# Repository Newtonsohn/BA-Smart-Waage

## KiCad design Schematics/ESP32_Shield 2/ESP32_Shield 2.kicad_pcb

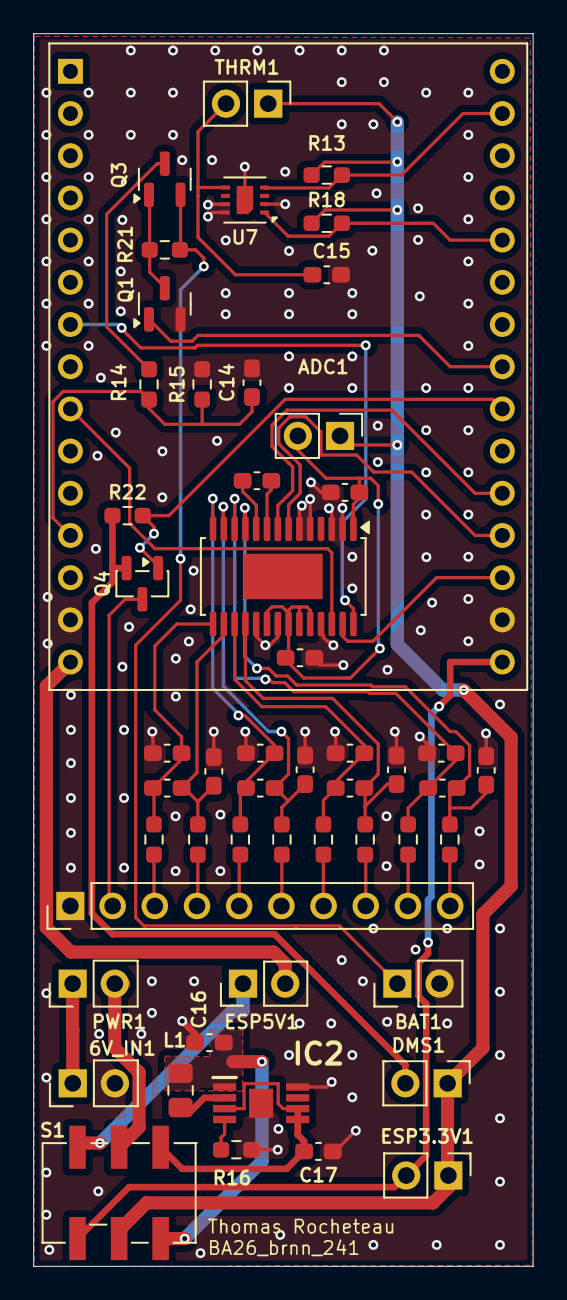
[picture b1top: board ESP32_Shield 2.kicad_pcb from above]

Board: 2 copper layers, 30.1 x 74.2 mm, 52 parts (0 on the bottom side), 46 nets.

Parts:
6V_IN1: Conn_01x02; PinHeader_1x02_P2.54mm_Vertical
ADC1: Conn_01x02; PinHeader_1x02_P2.54mm_Vertical
BAT1: Conn_01x02; PinHeader_1x02_P2.54mm_Vertical
C1, C12, C13, C14, C15: 0.1u; C_0603_1608Metric_Pad1.08x0.95mm_HandSolder
C16: 10u; C_0603_1608Metric_Pad1.08x0.95mm_HandSolder
C17: 4.7u; C_0603_1608Metric_Pad1.08x0.95mm_HandSolder
C18, C21, C24, C27: 1u; C_0603_1608Metric_Pad1.08x0.95mm_HandSolder
C19, C20, C22, C23, C25, C26, C28, C29: 10n; C_0603_1608Metric_Pad1.08x0.95mm_HandSolder
DMS1: Conn_01x02; PinHeader_1x02_P2.54mm_Vertical
ESP3.3V1, ESP5V1: Conn_01x02; PinHeader_1x02_P2.54mm_Vertical
IC2: TPS62842DGRR; SOP65P490X110-9N
J1: Conn_01x10; PinHeader_1x10_P2.54mm_Vertical
L1: 2.2u; C_0805_2012Metric_Pad1.18x1.45mm_HandSolder
PWR1: Conn_01x02; PinHeader_1x02_P2.54mm_Vertical
Q1: Si1308EDL; SOT-23
Q3, Q4: Si2319CDS; SOT-23
R13, R18: 10k; R_0603_1608Metric_Pad0.98x0.95mm_HandSolder
R14, R15, R21, R22: 100k; R_0603_1608Metric_Pad0.98x0.95mm_HandSolder
R16: 52.3k; R_0603_1608Metric_Pad0.98x0.95mm_HandSolder
R17, R19, R20, R23, R24, R25, R26, R27: 100; R_0603_1608Metric_Pad0.98x0.95mm_HandSolder
S1: JS202011SCQN; SW_DPDT_CK_JS202011JCQN
THRM1: Conn_01x02; PinHeader_1x02_P2.54mm_Vertical
U2: ESP32-C3-DevKitM-1
U6: ADS1234IPW; TSSOP-28-1EP_4.4x9.7mm_P0.65mm_EP2.74x4.75mm
U7: SHT30-DIS; Sensirion_DFN-8-1EP_2.5x2.5mm_P0.5mm_EP1.1x1.7mm

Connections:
3v3 BUCK: C16.2, IC2.1 (VOS), L1.1, S1.6
5V BUCK: C17.2, IC2.3 (MODE), IC2.5 (EN), IC2.6 (VIN), S1.3
5V LDO: ESP5V1.1, S1.1
!EN_DMS: Q4.1 (G), R22.1, U2.22 (IO17)
!PWDN: U2.9 (IO26), U6.26 (~PWDN)
+3.3V: ADC1.1, DMS1.1, ESP3.3V1.1, R13.2, R18.2, S1.5, THRM1.1
+5V: PWR1.2, S1.2
+BATT: BAT1.1, Q3.2 (S), R21.2
A0: U2.20 (IO4), U6.8 (A0)
A1: U2.19 (IO2), U6.7 (A1)
D_RDY_OUT: U2.7 (IO32), U6.28 (~DRDY/DOUT)
GND: 6V_IN1.2, BAT1.2, C1.1, C13.1, C14.1, C15.2, C16.1, C17.1, C19.1, C20.1, C22.1, C23.1, C25.1, C26.1, C28.1, C29.1, IC2.8 (GND_1), IC2.9 (GND_2), J1.1, Q1.2 (S), R15.1, R16.2, U2.14 (GND), U2.17 (GND), U6.2 (DGND), U6.3 (CLKIN/XTAL1), U6.5 (DGND), U6.6 (DGND), U6.19 (REFN), U6.21 (AGND), U6.25 (SPEED), U7.2 (ADDR), U7.7 (R), U7.8 (VSS), U7.9 (VSS)
N2: C24.1, C26.2, R25.2, U6.17 (AINN2)
N3: C21.1, C23.2, R23.2, U6.14 (AINN3)
N4: C18.1, C20.2, R17.2, U6.15 (AINN4)
unnamed: 6V_IN1.1, PWR1.1
unnamed: ADC1.2, C1.2, C13.2, U6.1 (DVDD), U6.20 (REFP), U6.22 (AVDD), U6.23 (GAIN0), U6.24 (GAIN1)
unnamed: C12.1, U6.10 (CAP)
unnamed: C12.2, U6.9 (CAP)
unnamed: DMS1.2, Q4.2 (S), R22.2
unnamed: ESP3.3V1.2, S1.4, U2.16 (3V3)
unnamed: ESP5V1.2, U2.15 (5V)
unnamed: IC2.2 (SW), L1.2
unnamed: IC2.4 (VSET), R16.1
unnamed: J1.2, Q4.3 (D)
unnamed: J1.3, R17.1
unnamed: J1.4, R19.1
unnamed: J1.5, R23.1
unnamed: J1.6, R20.1
unnamed: J1.7, R25.1
unnamed: J1.8, R24.1
unnamed: J1.9, R27.1
unnamed: J1.10, R26.1
unnamed: Q1.3 (D), Q3.1 (G), R21.1
unnamed: Q3.3 (D), R14.1
unnamed: C15.1, THRM1.2, U7.5 (VDD)
unnamed: C27.1, C29.2, R27.2, U6.12 (AINN1)
unnamed: C27.2, C28.2, R26.2, U6.11 (AINP1)
P2: C24.2, C25.2, R24.2, U6.18 (AINP2)
P3: C21.2, C22.2, R20.2, U6.13 (AINP3)
P4: C18.2, C19.2, R19.2, U6.16 (AINP4)
SCL: R13.1, U2.29 (IO23), U7.4 (SCL)
SCLK: U2.18 (IO15), U6.27 (SCLK)
SDA: R18.1, U2.26 (IO21), U7.1 (SDA)
bat_adc: C14.2, R14.2, R15.2, U2.12 (IO12)
en_meas: Q1.1 (G), U2.23 (IO5)

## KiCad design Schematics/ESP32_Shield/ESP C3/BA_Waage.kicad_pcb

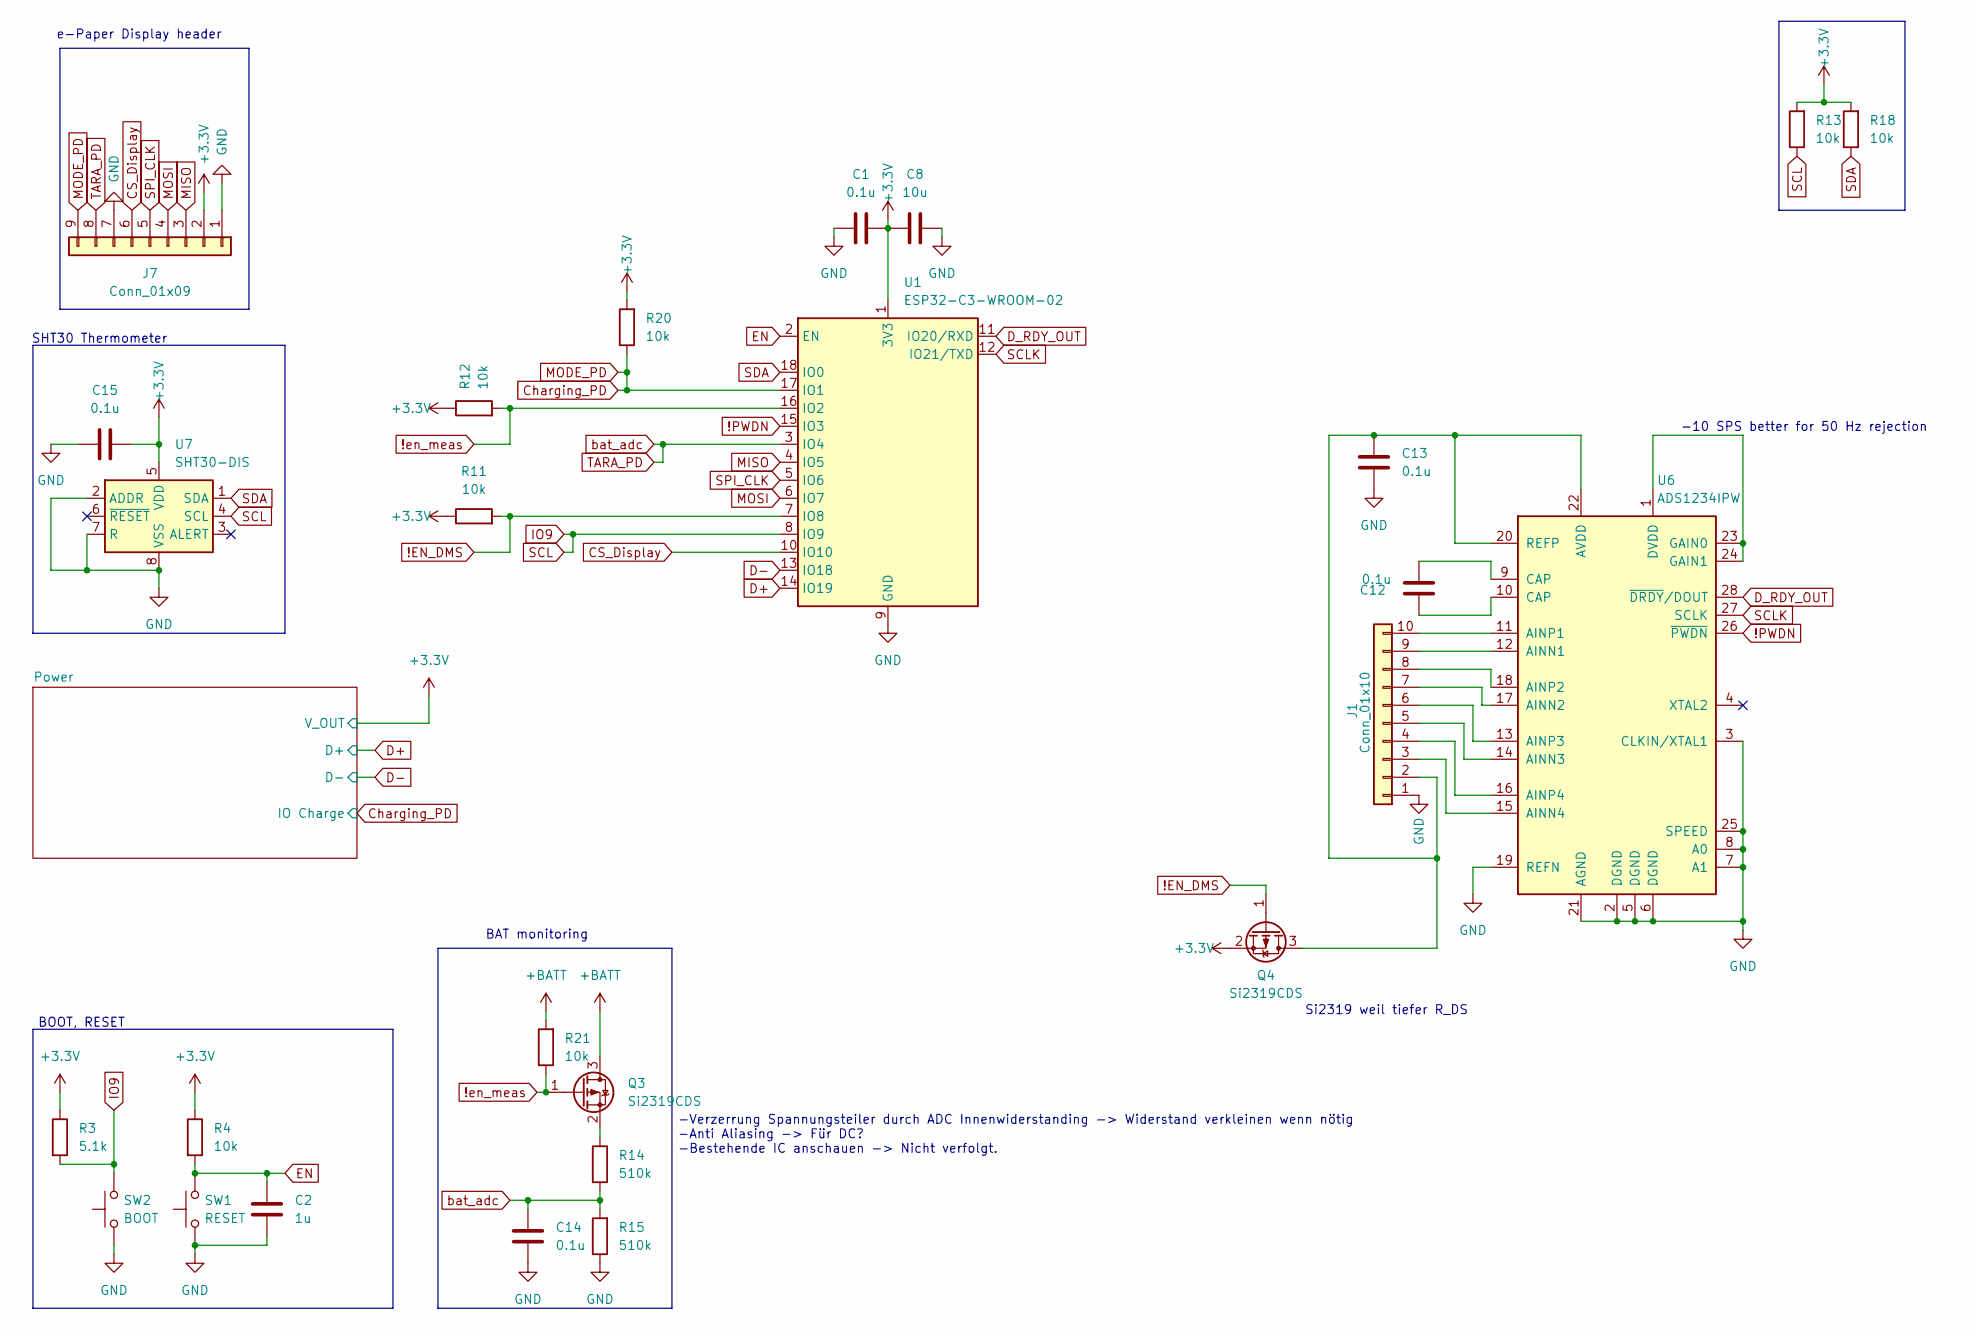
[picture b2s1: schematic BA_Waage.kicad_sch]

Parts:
C1, C12, C13, C14, C15: 0.1u; C_0603_1608Metric_Pad1.08x0.95mm_HandSolder
C2: 1u; C_0603_1608Metric_Pad1.08x0.95mm_HandSolder
C8: 10u; C_0603_1608Metric_Pad1.08x0.95mm_HandSolder
J1: Conn_01x10; PinHeader_1x10_P2.54mm_Vertical
J7: Conn_01x09; PinHeader_1x09_P2.54mm_Vertical
Q3, Q4: Si2319CDS; SOT-23
R3: 5.1k; R_0603_1608Metric_Pad0.98x0.95mm_HandSolder
R4, R11, R12, R13, R18, R20, R21: 10k; R_0603_1608Metric_Pad0.98x0.95mm_HandSolder
R14, R15: 510k; R_0603_1608Metric_Pad0.98x0.95mm_HandSolder
SW1: RESET; SW_Push_1P1T-SH_NO_CK_KMR2xxG
SW2: BOOT; SW_Push_1P1T-SH_NO_CK_KMR2xxG
U1: ESP32-C3-WROOM-02
U6: ADS1234IPW; TSSOP-28-1EP_4.4x9.7mm_P0.65mm_EP2.74x4.75mm
U7: SHT30-DIS; Sensirion_DFN-8-1EP_2.5x2.5mm_P0.5mm_EP1.1x1.7mm

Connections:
!EN_DMS: Q4.1 (G), R11.2, U1.7 (IO8)
!PWDN: U1.15 (IO3), U6.26 (~PWDN)
!en_meas: Q3.1 (G), R12.2, R21.1, U1.16 (IO2)
+3.3V: C1.2, C8.2, C15.1, J7.2, Q4.2 (S), R3.1, R4.1, R11.1, R12.1, R13.2, R18.2, R20.2, U1.1 (3V3), U7.5 (VDD); also elsewhere on the board
+BATT: Q3.3 (D), R21.2; also elsewhere on the board
CS_Display: J7.6, U1.10 (IO10)
Charging_PD: J7.9, R20.1, U1.17 (IO1); also elsewhere on the board
D+: U1.14 (IO19); also elsewhere on the board
D-: U1.13 (IO18); also elsewhere on the board
D_RDY_OUT: U1.11 (IO20/RXD), U6.28 (~DRDY/DOUT)
EN: C2.1, R4.2, SW1.2, U1.2 (EN)
GND: C1.1, C2.2, C8.1, C13.1, C14.1, C15.2, J1.1, J7.1, J7.7, R15.1, SW1.1, SW2.1, U1.9 (GND), U1.19 (GND), U6.2 (DGND), U6.3 (CLKIN/XTAL1), U6.5 (DGND), U6.6 (DGND), U6.7 (A1), U6.8 (A0), U6.19 (REFN), U6.21 (AGND), U6.25 (SPEED), U7.2 (ADDR), U7.7 (R), U7.8 (VSS), U7.9 (VSS); also elsewhere on the board
IO9: R3.2, R13.1, SW2.2, U1.8 (IO9), U7.4 (SCL)
MISO: J7.3, U1.4 (IO5)
MOSI: J7.4, U1.6 (IO7)
unnamed: C12.1, U6.10 (CAP)
unnamed: C12.2, U6.9 (CAP)
unnamed: C13.2, J1.2, Q4.3 (D), U6.20 (REFP), U6.22 (AVDD)
unnamed: J1.3, U6.15 (AINN4)
unnamed: J1.4, U6.16 (AINP4)
unnamed: J1.5, U6.14 (AINN3)
unnamed: J1.6, U6.13 (AINP3)
unnamed: J1.7, U6.17 (AINN2)
unnamed: J1.8, U6.18 (AINP2)
unnamed: J1.9, U6.12 (AINN1)
unnamed: J1.10, U6.11 (AINP1)
unnamed: Q3.2 (S), R14.1
unnamed: U6.1 (DVDD), U6.23 (GAIN0), U6.24 (GAIN1)
SCLK: U1.12 (IO21/TXD), U6.27 (SCLK)
SDA: R18.1, U1.18 (IO0), U7.1 (SDA)
SPI_CLK: J7.5, U1.5 (IO6)
TARA_PD: C14.2, J7.8, R14.2, R15.2, U1.3 (IO4)

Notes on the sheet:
Si2319 weil tiefer R_DS
-Verzerrung Spannungsteiler durch ADC Innenwiderstanding -> Widerstand verkleinen wenn nötig -Anti Aliasing -> Für DC? -Bestehende IC anschauen -> Nicht verfolgt.
SHT30 Thermometer
BAT monitoring
BOOT, RESET
e-Paper Display header
-10 SPS better for 50 Hz rejection

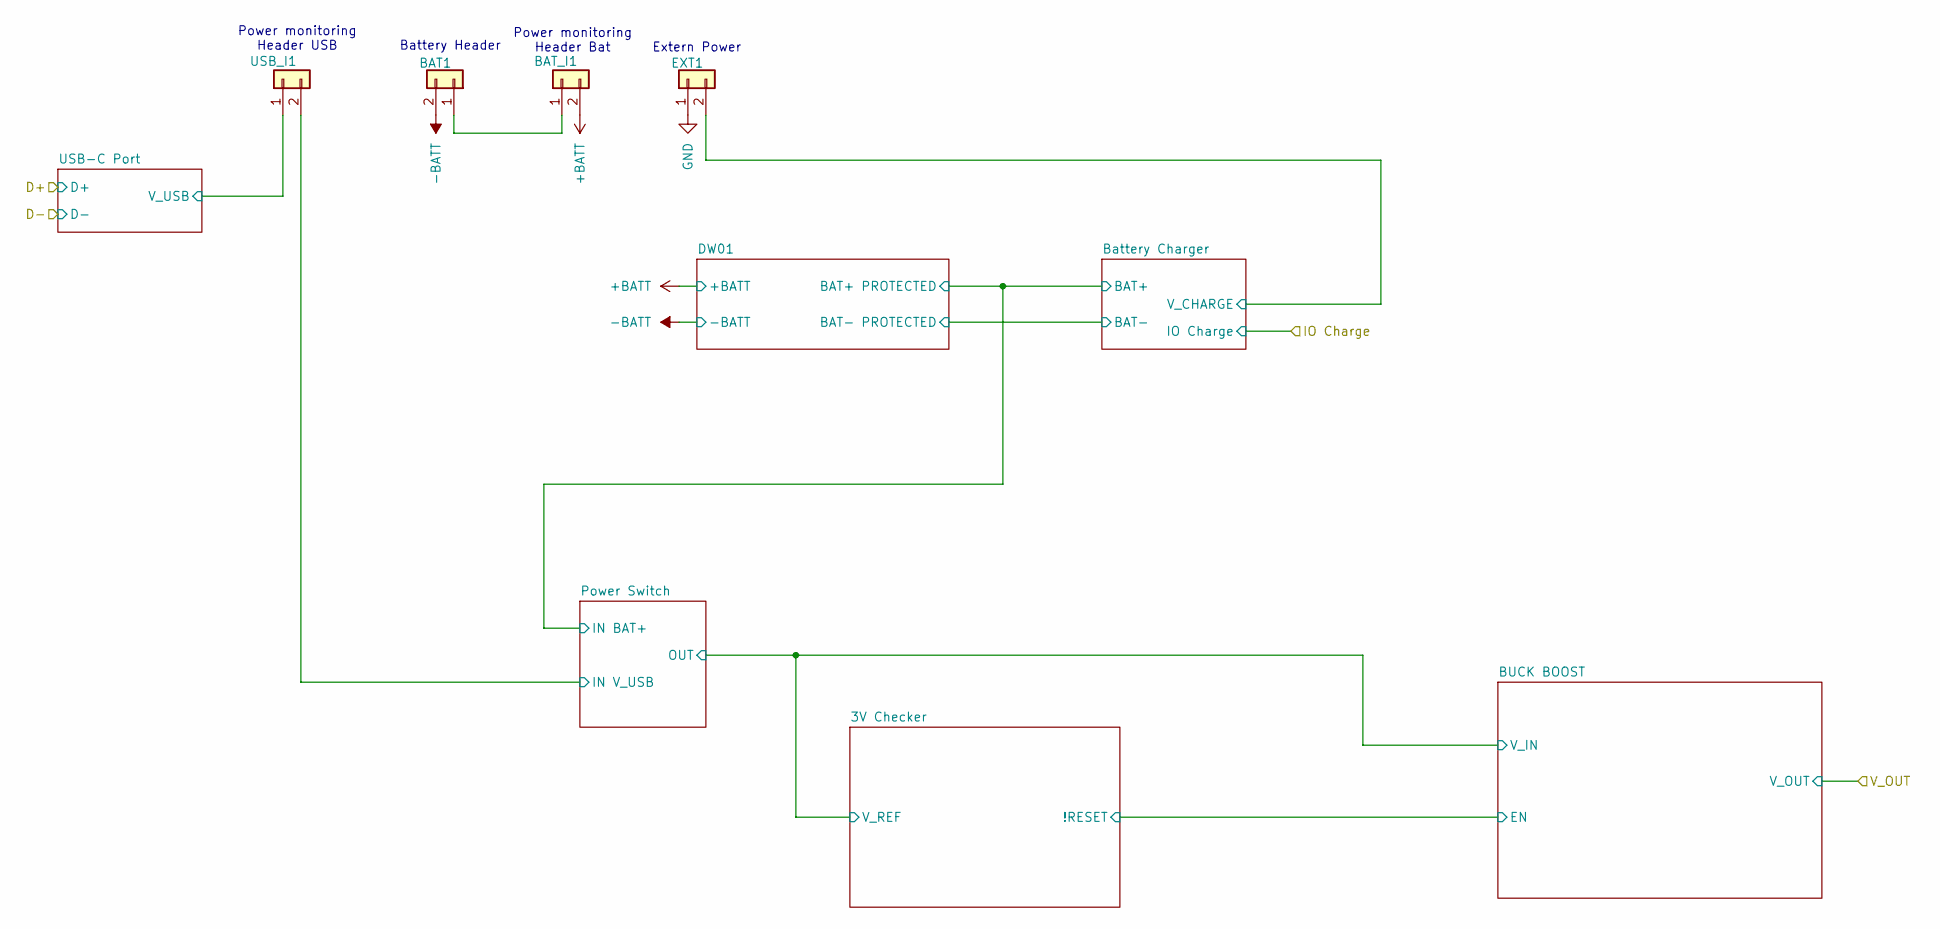
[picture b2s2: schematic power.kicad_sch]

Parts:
BAT1: Conn_01x02; PinHeader_1x02_P2.54mm_Vertical
BAT_I1: Conn_01x02; PinHeader_1x02_P2.54mm_Vertical
EXT1: Conn_01x02; PinHeader_1x02_P2.54mm_Vertical
USB_I1: Conn_01x02; PinHeader_1x02_P2.54mm_Vertical

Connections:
+BATT: BAT_I1.2; also elsewhere on the board
-BATT: BAT1.2; also elsewhere on the board
/Power/Battery Charger/V_CHARGE: EXT1.2; also elsewhere on the board
/Power/Power Switch/IN V_USB: USB_I1.2; also elsewhere on the board
GND: EXT1.1; also elsewhere on the board
unnamed: BAT1.1, BAT_I1.1
V_USB: USB_I1.1; also elsewhere on the board

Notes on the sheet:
Power monitoring Header USB
Power monitoring Header Bat
Extern Power
Battery Header

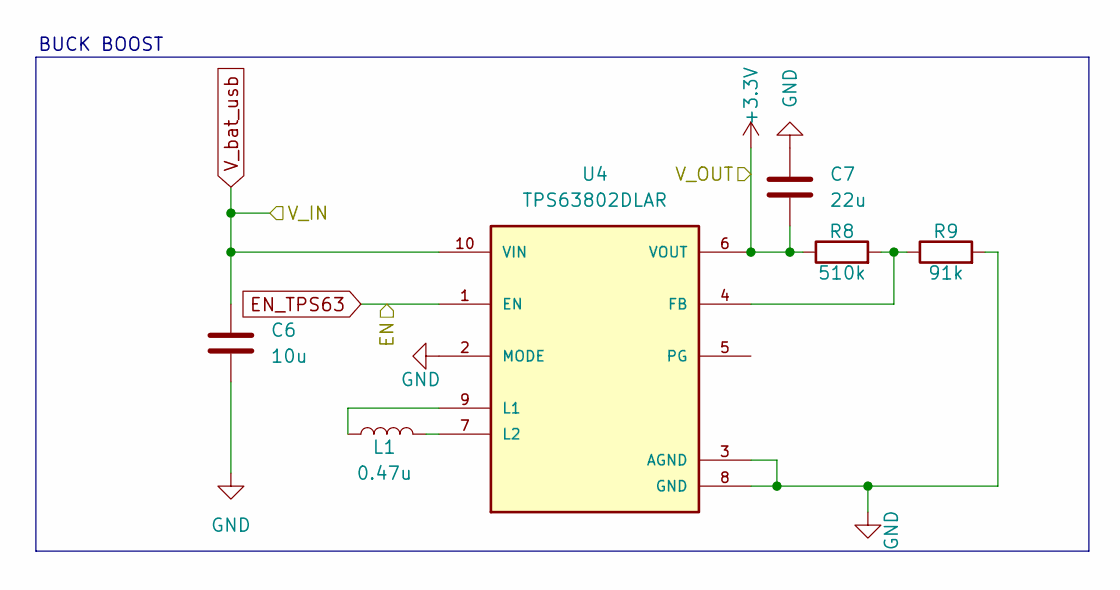
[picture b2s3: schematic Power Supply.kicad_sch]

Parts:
C6: 10u; C_0603_1608Metric_Pad1.08x0.95mm_HandSolder
C7: 22u; C_0603_1608Metric_Pad1.08x0.95mm_HandSolder
L1: 0.47u; L_Coilcraft_XxL4020
R8: 510k; R_0603_1608Metric_Pad0.98x0.95mm_HandSolder
R9: 91k; R_0603_1608Metric_Pad0.98x0.95mm_HandSolder
U4: TPS63802DLAR; VREG_TPS63802DLAR; PARTREV B

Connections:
+3.3V: C7.2, R8.1, U4.6 (VOUT); also elsewhere on the board
EN_TPS63: U4.1 (EN); also elsewhere on the board
GND: C6.2, C7.1, R9.2, U4.2 (MODE), U4.3 (AGND), U4.8 (GND); also elsewhere on the board
unnamed: R8.2, R9.1, U4.4 (FB)
unnamed: L1.1, U4.9 (L1)
unnamed: L1.2, U4.7 (L2)
V_bat_usb: C6.1, U4.10 (VIN); also elsewhere on the board

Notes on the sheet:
BUCK BOOST

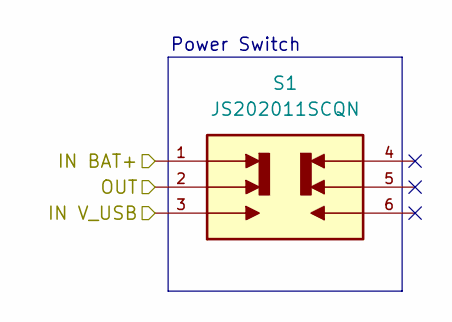
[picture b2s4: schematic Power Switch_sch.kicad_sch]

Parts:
S1: JS202011SCQN; SW_DPDT_CK_JS202011JCQN; PARTREV 26 May 22

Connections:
/Power/Power Switch/IN V_USB: S1.3; also elsewhere on the board
BAT+WD01: S1.1; also elsewhere on the board
V_bat_usb: S1.2; also elsewhere on the board

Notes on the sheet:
Power Switch

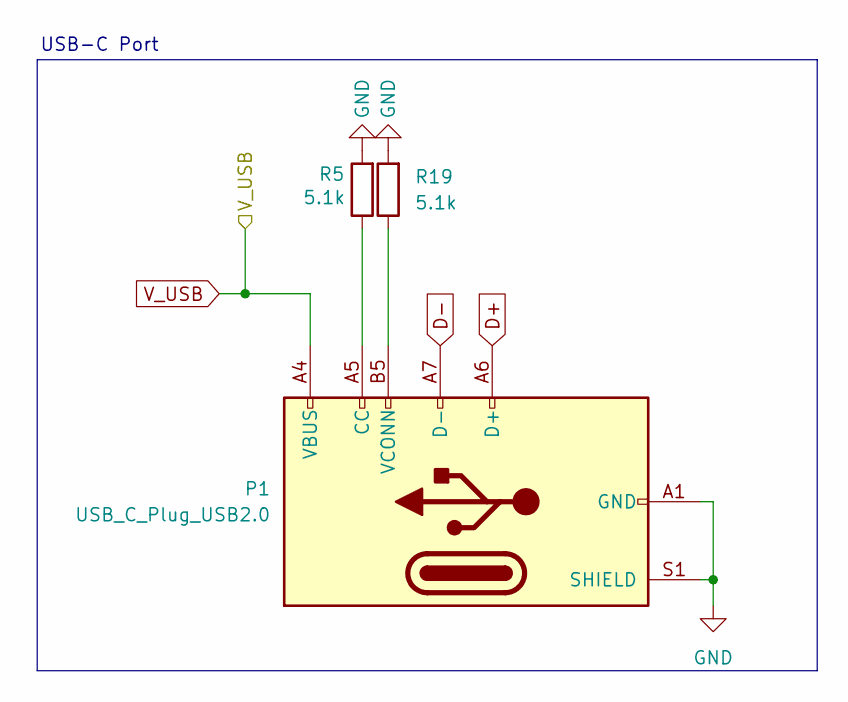
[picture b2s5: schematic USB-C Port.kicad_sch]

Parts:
P1: USB_C_Plug_USB2.0; USB_C_Receptacle_GCT_USB4105-xx-A_16P_TopMnt_Horizontal
R5, R19: 5.1k; R_0603_1608Metric_Pad0.98x0.95mm_HandSolder

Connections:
D+: P1.A6 (D+); also elsewhere on the board
D-: P1.A7 (D-); also elsewhere on the board
GND: P1.A1 (GND), P1.A12 (GND), P1.B1 (GND), P1.B12 (GND), P1.S1 (SHIELD), R5.2, R19.2; also elsewhere on the board
unnamed: P1.A5 (CC), R5.1
unnamed: P1.B5 (VCONN), R19.1
V_USB: P1.A4 (VBUS), P1.A9 (VBUS), P1.B4 (VBUS), P1.B9 (VBUS); also elsewhere on the board

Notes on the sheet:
USB-C Port

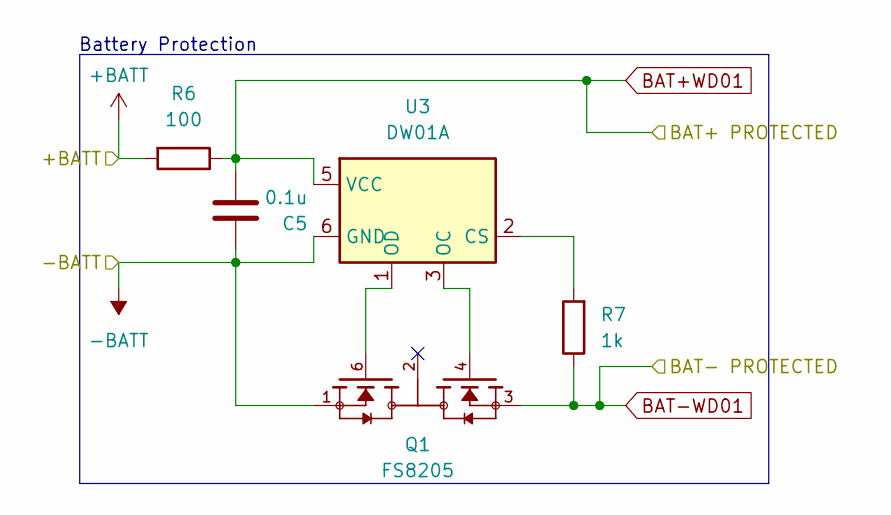
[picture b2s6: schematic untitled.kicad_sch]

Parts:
C5: 0.1u; C_0603_1608Metric_Pad1.08x0.95mm_HandSolder
Q1: FS8205; SOT95P280X145-6N; PARTREV 1.9
R6: 100; R_0603_1608Metric_Pad0.98x0.95mm_HandSolder
R7: 1k; R_0603_1608Metric_Pad0.98x0.95mm_HandSolder
U3: DW01A; SOT-23-6

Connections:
+BATT: R6.2; also elsewhere on the board
-BATT: C5.1, Q1.1, U3.6 (GND); also elsewhere on the board
BAT+WD01: C5.2, R6.1, U3.5 (VCC); also elsewhere on the board
GND: Q1.3, R7.1; also elsewhere on the board
unnamed: R7.2, U3.2 (CS)
unnamed: Q1.4, U3.3 (OC)
unnamed: Q1.6, U3.1 (OD)

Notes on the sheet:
Battery Protection

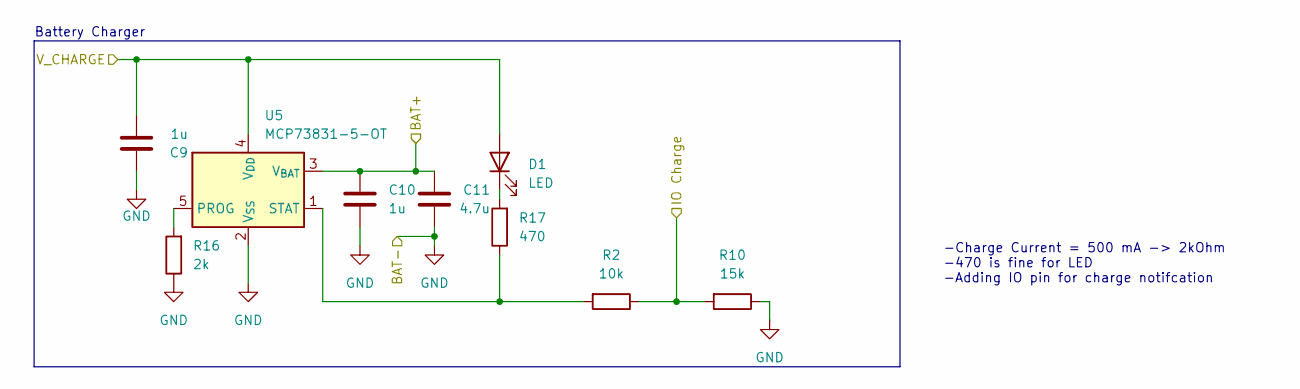
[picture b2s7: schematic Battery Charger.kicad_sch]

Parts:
C9, C10: 1u; C_0603_1608Metric_Pad1.08x0.95mm_HandSolder
C11: 4.7u; C_0603_1608Metric_Pad1.08x0.95mm_HandSolder
D1: LED; LED_0805_2012Metric_Pad1.15x1.40mm_HandSolder
R2: 10k; R_0603_1608Metric_Pad0.98x0.95mm_HandSolder
R10: 15k; R_0603_1608Metric_Pad0.98x0.95mm_HandSolder
R16: 2k; R_0603_1608Metric_Pad0.98x0.95mm_HandSolder
R17: 470; R_0603_1608Metric_Pad0.98x0.95mm_HandSolder
U5: MCP73831-5-OT; SOT-23-5

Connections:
/Power/Battery Charger/V_CHARGE: C9.2, D1.2 (A), U5.4 (V_{DD}); also elsewhere on the board
BAT+WD01: C10.1, C11.1, U5.3 (V_{BAT}); also elsewhere on the board
Charging_PD: R2.1, R10.2; also elsewhere on the board
GND: C9.1, C10.2, C11.2, R10.1, R16.1, U5.2 (V_{SS}); also elsewhere on the board
unnamed: D1.1 (K), R17.2
unnamed: R16.2, U5.5 (PROG)
unnamed: R2.2, R17.1, U5.1 (STAT)

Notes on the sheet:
Battery Charger
-Charge Current = 500 mA -> 2kOhm -470 is fine for LED -Adding IO pin for charge notifcation

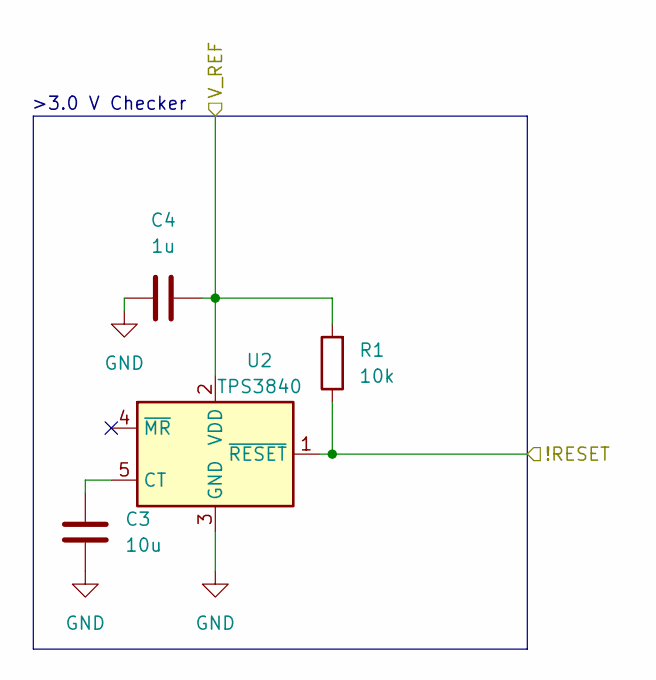
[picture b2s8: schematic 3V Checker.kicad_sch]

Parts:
C3: 10u; C_0603_1608Metric_Pad1.08x0.95mm_HandSolder
C4: 1u; C_0603_1608Metric_Pad1.08x0.95mm_HandSolder
R1: 10k; R_0603_1608Metric_Pad0.98x0.95mm_HandSolder
U2: TPS3840; SOT-23-5_HandSoldering

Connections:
EN_TPS63: R1.1, U2.1 (~RESET); also elsewhere on the board
GND: C3.1, C4.1, U2.3 (GND); also elsewhere on the board
unnamed: C3.2, U2.5 (CT)
V_bat_usb: C4.2, R1.2, U2.2 (VDD); also elsewhere on the board

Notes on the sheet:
>3.0 V Checker

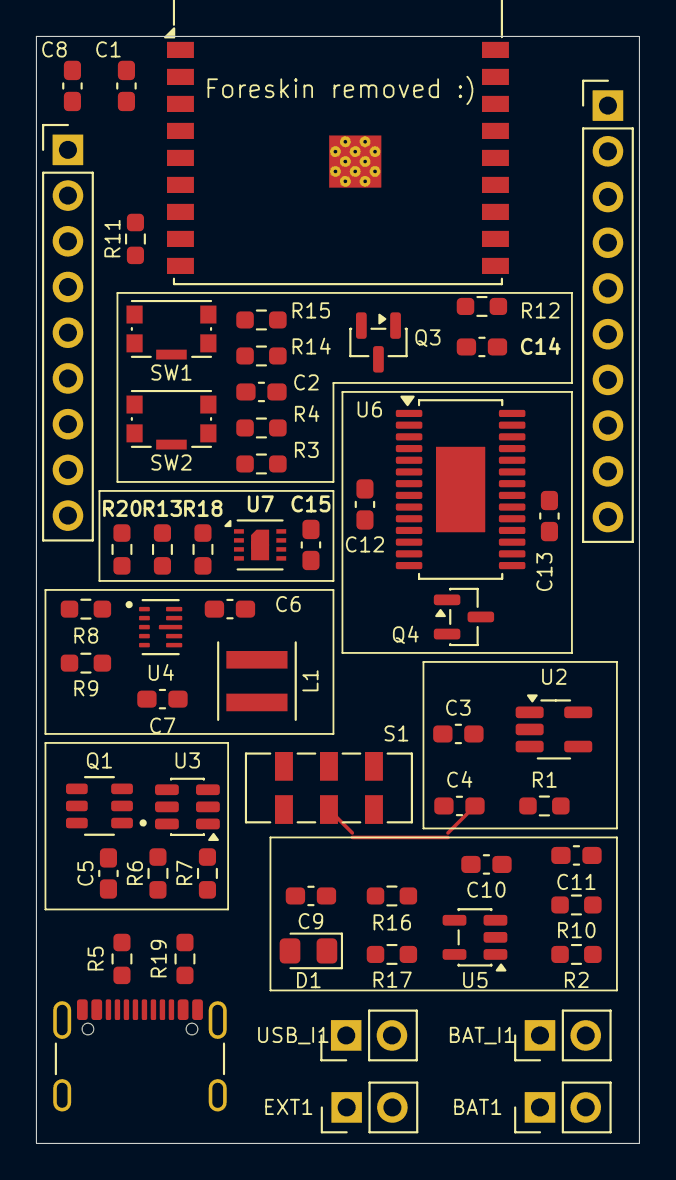
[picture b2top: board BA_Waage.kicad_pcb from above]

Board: 2 copper layers, 33.5 x 61.5 mm, 57 parts (0 on the bottom side), 52 nets.

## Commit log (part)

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2026-02-12 Add IndustrialScale firmware with BLE broadcast in SendDataState
2026-02-12 Commit backend
2026-03-02 upload hardware
2026-03-02 Order ready
2026-03-03 korrekturen
2026-03-06 Add RPi deployment config
2026-03-06 Increase keycloak healthcheck timeout for RPi
2026-03-06 Use Development env for Swagger on RPi
2026-03-10 updated battery voltage monitor mosfet schematics
2026-03-10 upload old PCB
2026-03-10 Feedback umetzen
2026-03-15 Add .gitignore and remove build artifacts from tracking
2026-03-15 gitignore
2026-03-18 Working advertisement
2026-03-20 50ms advertisement; 90%success rate on ble packages
2026-04-12 upload adc dbg
2026-04-16 ADS1234 Implementation
2026-04-18 ADS1234 implentation
2026-04-29 Further ADC debugging
2026-04-29 Doku
2026-05-06 Fix Keycloak Docker networking and update BLE Gateway
2026-05-06 ADC debbuging
2026-05-17 kicad libraries
2026-05-29 upload strommessungen
2026-05-31 Bilder upload
2026-06-03 Upload that shit
2026-06-05 backend upload
2026-06-05 back end upload
2026-06-21 UI improvement
2026-06-21 working calibration
2026-06-21 least square calibration
2026-06-23 Fixed light sleep during measuring
2026-06-23 improved UI
2026-06-23 Taring
2026-06-23 anpassung threshhold
